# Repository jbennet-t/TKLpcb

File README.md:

# TKLpcb
Through hole PCB for TKL keyboard.
My attempt at an open-source keyboard design, utilizing through hole components

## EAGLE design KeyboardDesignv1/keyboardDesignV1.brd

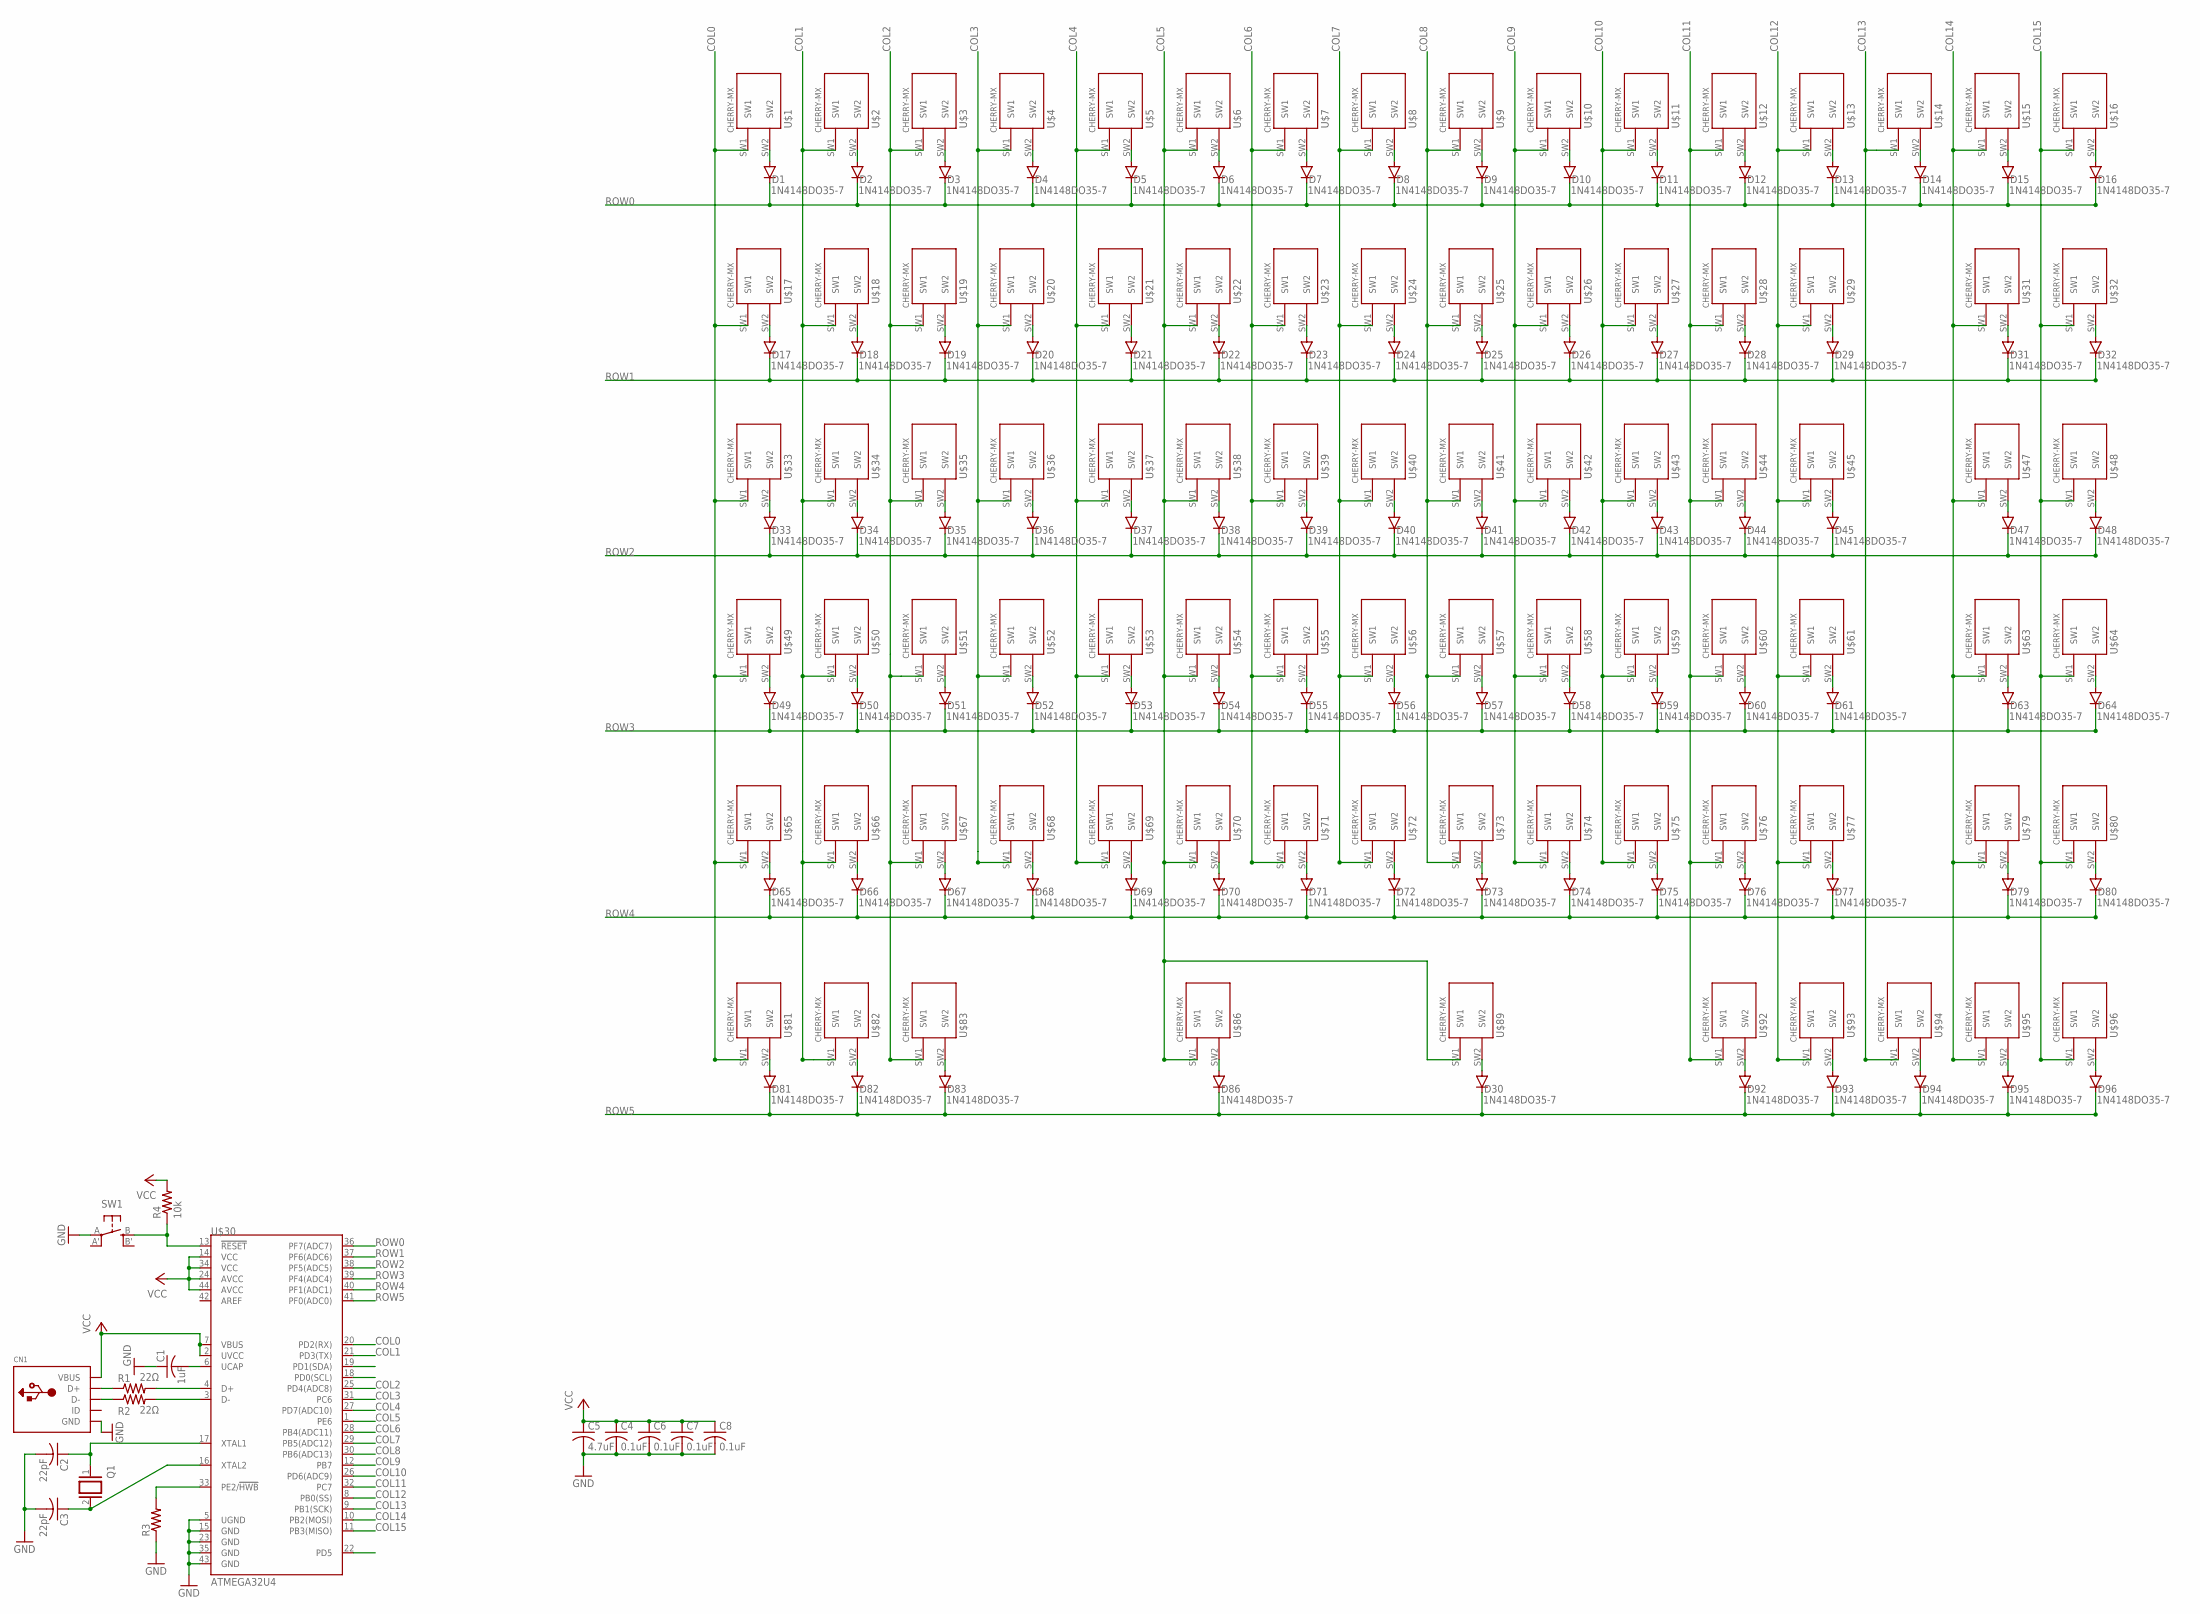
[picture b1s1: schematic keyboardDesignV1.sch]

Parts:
C1: 1uF; C025-025X050
C2, C3: 22pF; C025-025X050
C4, C6, C7, C8: 0.1uF; C025-025X050
C5: 4.7uF; C025-025X050
CN1: USBTHM; USB-MINIB-THM
D1, D2, D3, D4, D5, D6, D7, D8, D9, D10, D11, D12, D13, D14, D15, D16, D17, D18, D19, D20, D21, D22, D23, D24, D25, D26, D27, D28, D29, D30, D31, D32, D33, D34, D35, D36, D37, D38, D39, D40, D41, D42, D43, D44, D45, D47, D48, D49, D50, D51, D52, D53, D54, D55, D56, D57, D58, D59, D60, D61, D63, D64, D65, D66, D67, D68, D69, D70, D71, D72, D73, D74, D75, D76, D77, D79, D80, D81, D82, D83, D86, D92, D93, D94, D95, D96: 1N4148DO35-7; DO35-7
Q1: XTAL/S; QS
R1, R2: 22Ω; 0204/7
R3: R-US_0204/7; 0204/7
R4: 10k; 0204/7
SW1: SPST_TACT-EVQQ2; EVQ-Q2
U$1, U$2, U$3, U$4, U$5, U$6, U$7, U$8, U$9, U$10, U$11, U$12, U$13, U$14, U$15, U$16, U$17, U$18, U$19, U$20, U$21, U$22, U$23, U$24, U$25, U$26, U$27, U$28, U$29, U$31, U$32, U$33, U$34, U$35, U$36, U$37, U$38, U$39, U$40, U$41, U$42, U$43, U$44, U$45, U$47, U$48, U$49, U$50, U$51, U$52, U$53, U$54, U$55, U$56, U$57, U$58, U$59, U$60, U$61, U$63, U$64, U$65, U$66, U$67, U$68, U$69, U$70, U$71, U$72, U$73, U$74, U$75, U$76, U$77, U$79, U$80, U$81, U$82, U$83, U$86, U$89, U$92, U$93, U$94, U$95, U$96: CHERRY-MXSTANDARD; CHERRY-MX
U$30: ATMEGA32U4; QFN-44-NOPAD_1:1

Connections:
COL0: U$1.SW1, U$17.SW1, U$30.20 (PD2(RX)), U$33.SW1, U$49.SW1, U$65.SW1, U$81.SW1
COL1: U$2.SW1, U$18.SW1, U$30.21 (PD3(TX)), U$34.SW1, U$50.SW1, U$66.SW1, U$82.SW1
COL2: U$3.SW1, U$19.SW1, U$30.25 (PD4(ADC8)), U$35.SW1, U$51.SW1, U$67.SW1, U$83.SW1
COL3: U$4.SW1, U$20.SW1, U$30.31 (PC6), U$36.SW1, U$52.SW1, U$68.SW1
COL4: U$5.SW1, U$21.SW1, U$30.27 (PD7(ADC10)), U$37.SW1, U$53.SW1, U$69.SW1
COL5: U$6.SW1, U$22.SW1, U$30.1 (PE6), U$38.SW1, U$54.SW1, U$70.SW1, U$86.SW1, U$89.SW1
COL6: U$7.SW1, U$23.SW1, U$30.28 (PB4(ADC11)), U$39.SW1, U$55.SW1, U$71.SW1
COL7: U$8.SW1, U$24.SW1, U$30.29 (PB5(ADC12)), U$40.SW1, U$56.SW1, U$72.SW1
COL8: U$9.SW1, U$25.SW1, U$30.30 (PB6(ADC13)), U$41.SW1, U$57.SW1, U$73.SW1
COL9: U$10.SW1, U$26.SW1, U$30.12 (PB7), U$42.SW1, U$58.SW1, U$74.SW1
COL10: U$11.SW1, U$27.SW1, U$30.26 (PD6(ADC9)), U$43.SW1, U$59.SW1, U$75.SW1
COL11: U$12.SW1, U$28.SW1, U$30.32 (PC7), U$44.SW1, U$60.SW1, U$76.SW1, U$92.SW1
COL12: U$13.SW1, U$29.SW1, U$30.8 (PB0(SS)), U$45.SW1, U$61.SW1, U$77.SW1, U$93.SW1
COL13: U$14.SW1, U$30.9 (PB1(SCK)), U$94.SW1
COL14: U$15.SW1, U$30.10 (PB2(MOSI)), U$31.SW1, U$47.SW1, U$63.SW1, U$79.SW1, U$95.SW1
COL15: U$16.SW1, U$30.11 (PB3(MISO)), U$32.SW1, U$48.SW1, U$64.SW1, U$80.SW1, U$96.SW1
GND: C1.1, C2.2, C3.2, C4.2, C5.2, C6.2, C7.2, C8.2, CN1.GND, R3.1, SW1.A, U$30.5 (UGND), U$30.15 (GND), U$30.23 (GND), U$30.35 (GND), U$30.43 (GND)
unnamed: D1.A, U$1.SW2
unnamed: D30.A, U$89.SW2
unnamed: D17.A, U$17.SW2
unnamed: D2.A, U$2.SW2
unnamed: C1.2, U$30.6 (UCAP)
unnamed: R1.2, U$30.4 (D+)
unnamed: D3.A, U$3.SW2
unnamed: CN1.D+, R1.1
unnamed: D18.A, U$18.SW2
unnamed: D4.A, U$4.SW2
unnamed: R2.2, U$30.3 (D-)
unnamed: CN1.D-, R2.1
unnamed: D5.A, U$5.SW2
unnamed: C2.1, Q1.1, U$30.17 (XTAL1)
unnamed: D19.A, U$19.SW2
unnamed: D6.A, U$6.SW2
unnamed: C3.1, Q1.2, U$30.16 (XTAL2)
unnamed: R3.2, U$30.33 (PE2/!HWB)
unnamed: D7.A, U$7.SW2
unnamed: R4.1, SW1.B (S), U$30.13 (!RESET)
unnamed: D20.A, U$20.SW2
unnamed: D8.A, U$8.SW2
unnamed: D9.A, U$9.SW2
unnamed: D21.A, U$21.SW2
unnamed: D10.A, U$10.SW2
unnamed: D11.A, U$11.SW2
unnamed: D22.A, U$22.SW2
unnamed: D12.A, U$12.SW2
unnamed: D13.A, U$13.SW2
unnamed: D23.A, U$23.SW2
unnamed: D14.A, U$14.SW2
unnamed: D15.A, U$15.SW2
unnamed: D24.A, U$24.SW2
unnamed: D16.A, U$16.SW2
unnamed: D25.A, U$25.SW2
unnamed: D26.A, U$26.SW2
unnamed: D27.A, U$27.SW2
unnamed: D28.A, U$28.SW2
unnamed: D29.A, U$29.SW2
unnamed: D31.A, U$31.SW2
unnamed: D32.A, U$32.SW2
unnamed: D33.A, U$33.SW2
unnamed: D34.A, U$34.SW2
unnamed: D35.A, U$35.SW2
unnamed: D36.A, U$36.SW2
unnamed: D37.A, U$37.SW2
unnamed: D38.A, U$38.SW2
unnamed: D39.A, U$39.SW2
unnamed: D40.A, U$40.SW2
unnamed: D41.A, U$41.SW2
unnamed: D42.A, U$42.SW2
unnamed: D43.A, U$43.SW2
unnamed: D44.A, U$44.SW2
unnamed: D45.A, U$45.SW2
unnamed: D47.A, U$47.SW2
unnamed: D48.A, U$48.SW2
unnamed: D49.A, U$49.SW2
unnamed: D50.A, U$50.SW2
unnamed: D51.A, U$51.SW2
unnamed: D52.A, U$52.SW2
unnamed: D53.A, U$53.SW2
unnamed: D54.A, U$54.SW2
unnamed: D55.A, U$55.SW2
unnamed: D56.A, U$56.SW2
unnamed: D57.A, U$57.SW2
unnamed: D58.A, U$58.SW2
unnamed: D59.A, U$59.SW2
unnamed: D60.A, U$60.SW2
unnamed: D61.A, U$61.SW2
unnamed: D63.A, U$63.SW2
unnamed: D64.A, U$64.SW2
unnamed: D65.A, U$65.SW2
unnamed: D66.A, U$66.SW2
unnamed: D67.A, U$67.SW2
unnamed: D68.A, U$68.SW2
unnamed: D69.A, U$69.SW2
unnamed: D70.A, U$70.SW2
unnamed: D71.A, U$71.SW2
unnamed: D72.A, U$72.SW2
unnamed: D73.A, U$73.SW2
unnamed: D74.A, U$74.SW2
unnamed: D75.A, U$75.SW2
unnamed: D76.A, U$76.SW2
unnamed: D77.A, U$77.SW2
unnamed: D79.A, U$79.SW2
unnamed: D80.A, U$80.SW2
unnamed: D81.A, U$81.SW2
unnamed: D82.A, U$82.SW2
unnamed: D83.A, U$83.SW2
unnamed: D86.A, U$86.SW2
unnamed: D92.A, U$92.SW2
unnamed: D93.A, U$93.SW2
unnamed: D94.A, U$94.SW2
unnamed: D95.A, U$95.SW2
unnamed: D96.A, U$96.SW2
ROW0: D1.C, D2.C, D3.C, D4.C, D5.C, D6.C, D7.C, D8.C, D9.C, D10.C, D11.C, D12.C, D13.C, D14.C, D15.C, D16.C, U$30.36 (PF7(ADC7))
ROW1: D17.C, D18.C, D19.C, D20.C, D21.C, D22.C, D23.C, D24.C, D25.C, D26.C, D27.C, D28.C, D29.C, D31.C, D32.C, U$30.37 (PF6(ADC6))
ROW2: D33.C, D34.C, D35.C, D36.C, D37.C, D38.C, D39.C, D40.C, D41.C, D42.C, D43.C, D44.C, D45.C, D47.C, D48.C, U$30.38 (PF5(ADC5))
ROW3: D49.C, D50.C, D51.C, D52.C, D53.C, D54.C, D55.C, D56.C, D57.C, D58.C, D59.C, D60.C, D61.C, D63.C, D64.C, U$30.39 (PF4(ADC4))
ROW4: D65.C, D66.C, D67.C, D68.C, D69.C, D70.C, D71.C, D72.C, D73.C, D74.C, D75.C, D76.C, D77.C, D79.C, D80.C, U$30.40 (PF1(ADC1))
ROW5: D30.C, D81.C, D82.C, D83.C, D86.C, D92.C, D93.C, D94.C, D95.C, D96.C, U$30.41 (PF0(ADC0))
VCC: C4.1, C5.1, C6.1, C7.1, C8.1, CN1.VBUS, R4.2, U$30.2 (UVCC), U$30.7 (VBUS), U$30.14 (VCC), U$30.24 (AVCC), U$30.34 (VCC), U$30.44 (AVCC)

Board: 2 copper layers, 188 parts (0 on the bottom side), 119 nets, no tracks yet.

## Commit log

2019-09-01 first commit of keyboard pcb files

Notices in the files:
parts and their libraries:
SparkFun-IC-Microcontroller: Licensing: Creative Commons ShareAlike 4.0 International - https://creativecommons.org/licenses/by-sa/4.0
